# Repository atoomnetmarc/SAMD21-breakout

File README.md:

ATSAMD21G18A-AU breakout board with the physical layout inspired by the `Arduino MKR Zero`.

# Power supply

Supply power to 3V3 pin. Or supply power to 5V pin (or USB) and get free 3V3.

# Platformio

`platformio.ini`:
```ini
[env:mzeroUSB]
platform = atmelsam
board = mzeroUSB
```

# Pinout

| Arduino   | SAMD21    | Alternate |
| --:       | --:       | --:       |
| AREF      | PA03      |
| A0        | PA01      | DAC
| A1        | PB08      |
| A2        | PB09      |
| A3        | PA04      |
| A4        | PA05      |
| A5        | PB02      |
| RX        | PA11      | D0
| TX        | PA10      | D1
| ~D2       | PA08      | SDA2
| ~D3       | PA09      | SCL2
| ~D4       | PA14      |
| ~D5       | PA15      |
| D6        | PA20      |
| D7        | PA21      |
| ~D8       | PA06      |
| ~D9       | PA07      |
| ~D10      | PA18      |
| ~D11      | PA16      | SDA3
| ~D12      | PA19      |
| ~D13      | PA17      | SCL3
| SDA       | PA22      |
| SCL       | PA23      |
| MISO      | PA12      |
| MOSI      | PB10      |
| SCK       | PB11      |

# Soldering

Solder every component except U1, J2, J4 and J5. Begin with all the components on the bottom.

Clean board.

Apply current limited (50mA) 5V to GND and 5V pin. Current should be about 6mA. Measure voltage on 3V3 pin, it should be 3.3V. Disconnect. Connect USB, both LEDs should light up again.

Solder U1 carefully. Inspect U1 pins with microscope for shorts or missing soldered pins. Correct when found.

Clean again. Inspect again.

Measure all adjacent signal pins (on headers J4 and J5) for shorts: XIN21, XOUT32, A0, AREF, GND, 3V3, A1, A2, A3, A4, ~D8, ~D9, ~D2, ~D3, TX, RX, 3V3, GND, MOSI, SCK, MISO, PA13 (U1 pin 22), ~D4, ~D5, ~D11, ~D13, ~D10, ~D12, D6, D7, SDA, SCL, USB- (on D1), USB+ (on D2), GND, 3V3, PB22 (U1 pin 37), PB23 (U1 pin 38), PA27 (U1 pin 39), RST, PA28 (U1 pin 41), GND, VDDCORE (on C21), 3V3, CLK (on J2), DIO (on J2), A5 and PB03 (U1 pin 48). Correct shorts when found.

Apply current limited (50mA) to GND and 5V pin. Current should still be about 6mA.

# Bootloader

Before this board behaves like an `Arduino M0` (that you can program with the USB-port) you must first use the `Burn Bootloader`-function from the Arduino IDE. Choose the board `Arduino M0`, then choose your desired `Programmer` then choose `Burn Bootloader`.

# Invisible Blink

Connect USB. A new serial port should appear in the device manager.

Open the example Blink sketch and flash it to the MCU. Measure voltage on GND and ~D13, it should alternate between 0V and 3.3V.

# Done

Done!

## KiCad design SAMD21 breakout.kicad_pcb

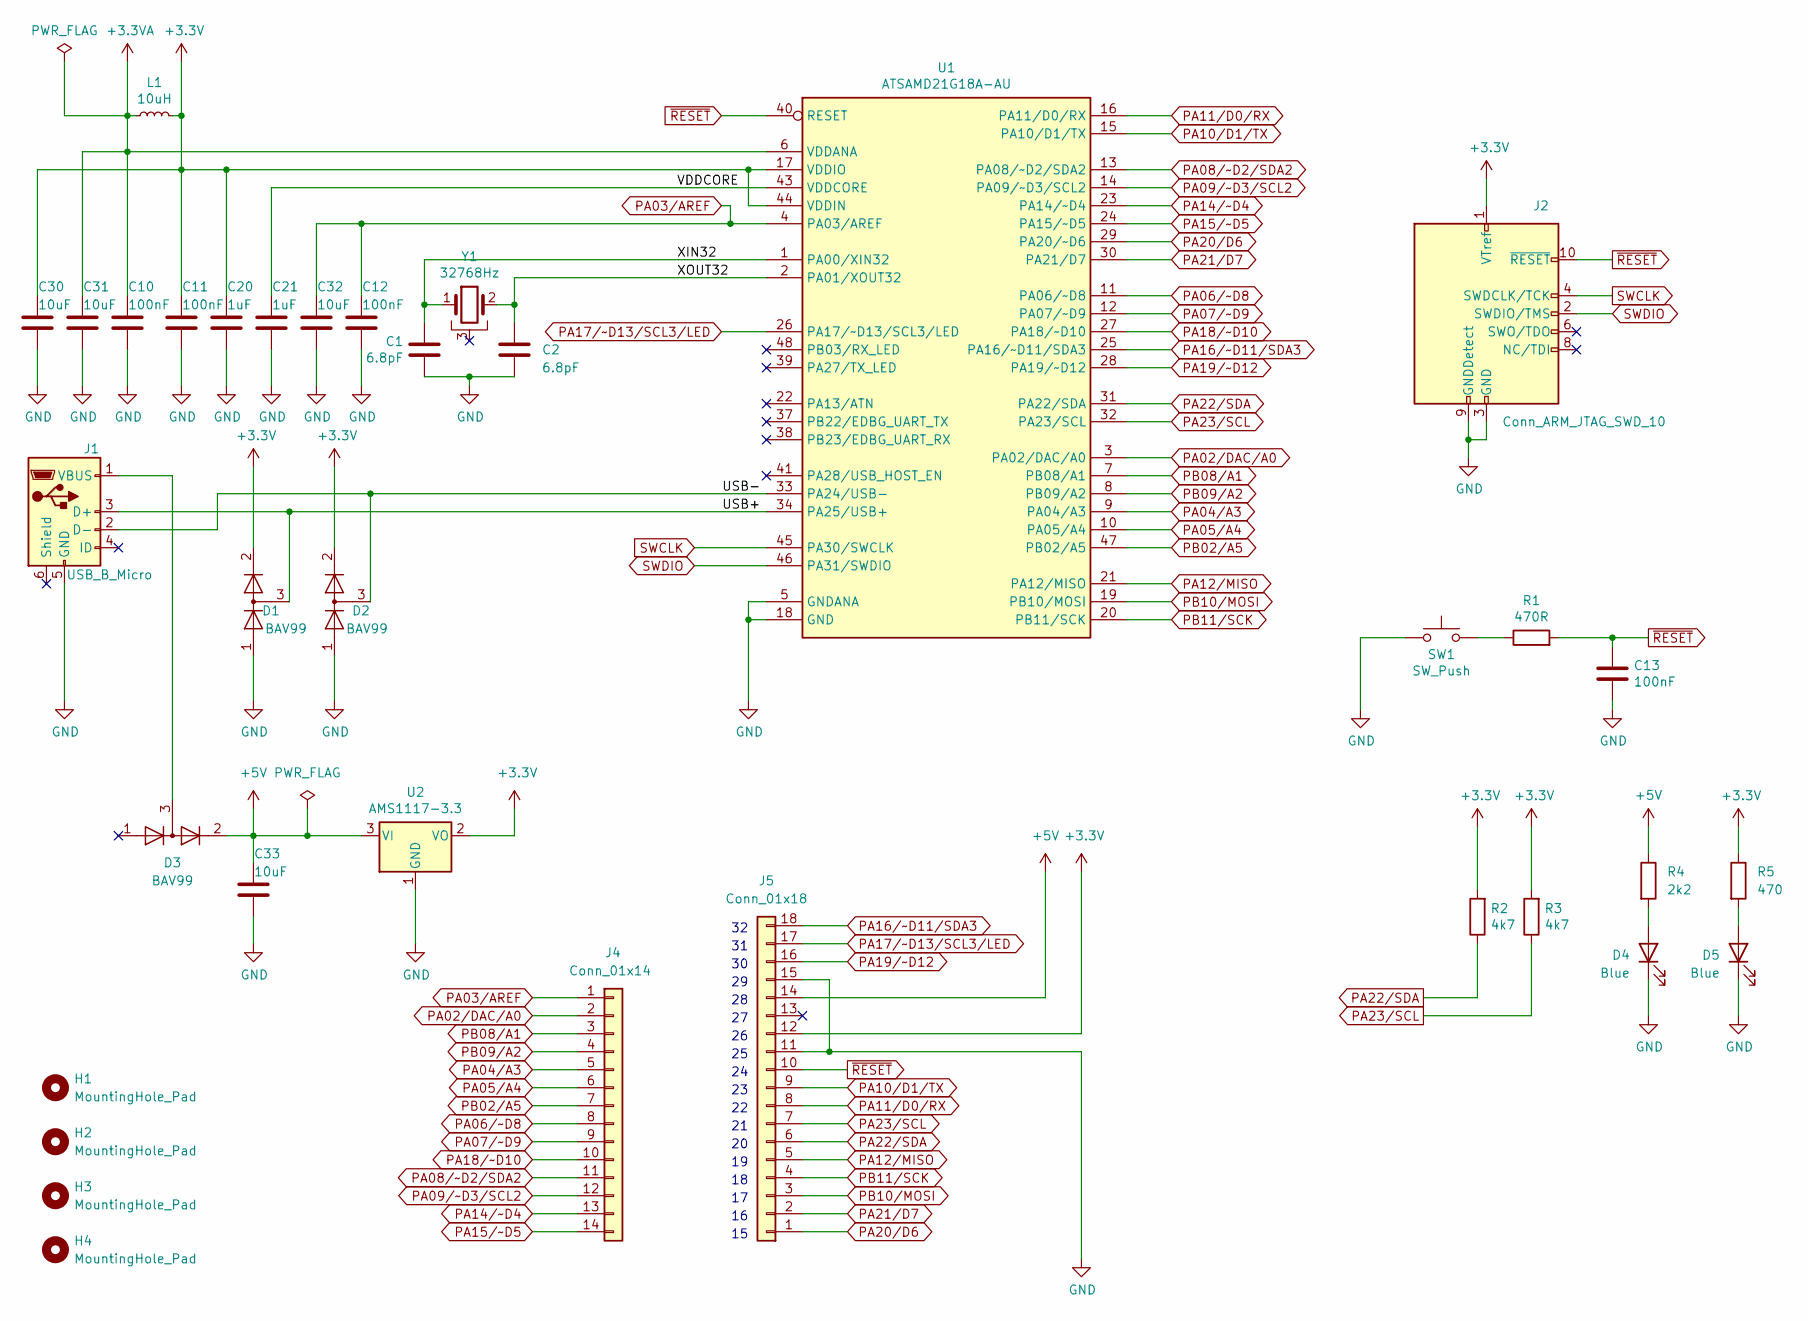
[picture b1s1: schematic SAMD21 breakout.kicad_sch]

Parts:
C1, C2: 6.8pF; C_0805_2012Metric_Pad1.18x1.45mm_HandSolder
C10, C11, C12, C13: 100nF; C_0805_2012Metric_Pad1.18x1.45mm_HandSolder
C20, C21: 1uF; C_0805_2012Metric_Pad1.18x1.45mm_HandSolder
C30, C31, C32, C33: 10uF; C_0805_2012Metric_Pad1.18x1.45mm_HandSolder
D1, D2, D3: BAV99; SOT-23
D4, D5: Blue; LED_0805_2012Metric_Pad1.15x1.40mm_HandSolder
H1, H2, H3, H4: MountingHole_Pad; MountingHole_2.2mm_M2_DIN965
J1: USB_B_Micro; USB_Micro-B_Amphenol_10118194_Horizontal
J2: Conn_ARM_JTAG_SWD_10; PinHeader_2x05_P2.54mm_Vertical
J4: Conn_01x14; PinHeader_1x14_P2.54mm_Vertical
J5: Conn_01x18; PinHeader_1x18_P2.54mm_Vertical
L1: 10uH; L_0805_2012Metric_Pad1.15x1.40mm_HandSolder
R1: 470R; R_0805_2012Metric_Pad1.20x1.40mm_HandSolder
R2, R3: 4k7; R_0805_2012Metric_Pad1.20x1.40mm_HandSolder
R4: 2k2; R_0805_2012Metric_Pad1.20x1.40mm_HandSolder
R5: 470; R_0805_2012Metric_Pad1.20x1.40mm_HandSolder
SW1: SW_Push; SW_SPST_CK_RS282G05A3
U1: ATSAMD21G18A-AU; TQFP-48_7x7mm_P0.5mm
U2: AMS1117-3.3; SOT-223-3_TabPinNC
Y1: 32768Hz; Crystal_C26-LF_D2.1mm_L6.5mm_Horizontal_1EP_style1

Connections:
+3.3V: C11.1, C20.1, C30.1, D1.2 (A), D2.2 (A), J2.1 (VTref), J5.12, L1.2, R2.2, R3.2, R5.1, U1.17 (VDDIO), U1.36 (VDDIO), U1.44 (VDDIN), U2.2 (VO)
+3.3VA: C10.1, C31.1, L1.1, U1.6 (VDDANA)
+5V: C33.1, D3.2 (A), J5.14, R4.1, U2.3 (VI)
/USB+: D1.3 (K), J1.3 (D+), U1.34 (PA25/USB+)
/USB-: D2.3 (K), J1.2 (D-), U1.33 (PA24/USB-)
/VDDCORE: C21.1, U1.43 (VDDCORE)
/XIN32: C1.1, U1.1 (PA00/XIN32), Y1.1
/XOUT32: C2.1, U1.2 (PA01/XOUT32), Y1.2
GND: C1.2, C2.2, C10.2, C11.2, C12.2, C13.2, C20.2, C21.2, C30.2, C31.2, C32.2, C33.2, D1.1 (K), D2.1 (K), D4.1 (K), D5.1 (K), J1.5 (GND), J2.3 (GND), J2.5 (GND), J2.9 (GNDDetect), J5.11, J5.15, SW1.1, U1.5 (GNDANA), U1.18 (GND), U1.35 (GND), U1.42 (GND), U2.1 (GND)
unnamed: D3.3 (K), J1.1 (VBUS)
unnamed: D4.2 (A), R4.2
unnamed: D5.2 (A), R5.2
unnamed: R1.1, SW1.2
PA02/DAC/A0: J4.2, U1.3 (PA02/DAC/A0)
PA03/AREF: C12.1, C32.1, J4.1, U1.4 (PA03/AREF)
PA04/A3: J4.5, U1.9 (PA04/A3)
PA05/A4: J4.6, U1.10 (PA05/A4)
PA06/~D8: J4.8, U1.11 (PA06/~D8)
PA07/~D9: J4.9, U1.12 (PA07/~D9)
PA08/~D2/SDA2: J4.11, U1.13 (PA08/~D2/SDA2)
PA09/~D3/SCL2: J4.12, U1.14 (PA09/~D3/SCL2)
PA10/D1/TX: J5.9, U1.15 (PA10/D1/TX)
PA11/D0/RX: J5.8, U1.16 (PA11/D0/RX)
PA12/MISO: J5.5, U1.21 (PA12/MISO)
PA14/~D4: J4.13, U1.23 (PA14/~D4)
PA15/~D5: J4.14, U1.24 (PA15/~D5)
PA16/~D11/SDA3: J5.18, U1.25 (PA16/~D11/SDA3)
PA17/~D13/SCL3/LED: J5.17, U1.26 (PA17/~D13/SCL3/LED)
PA18/~D10: J4.10, U1.27 (PA18/~D10)
PA19/~D12: J5.16, U1.28 (PA19/~D12)
PA20/D6: J5.1, U1.29 (PA20/~D6)
PA21/D7: J5.2, U1.30 (PA21/D7)
PA22/SDA: J5.6, R2.1, U1.31 (PA22/SDA)
PA23/SCL: J5.7, R3.1, U1.32 (PA23/SCL)
PB02/A5: J4.7, U1.47 (PB02/A5)
PB08/A1: J4.3, U1.7 (PB08/A1)
PB09/A2: J4.4, U1.8 (PB09/A2)
PB10/MOSI: J5.3, U1.19 (PB10/MOSI)
PB11/SCK: J5.4, U1.20 (PB11/SCK)
SWCLK: J2.4 (SWDCLK/TCK), U1.45 (PA30/SWCLK)
SWDIO: J2.2 (SWDIO/TMS), U1.46 (PA31/SWDIO)
~RESET: C13.1, J2.10 (~RESET), J5.10, R1.2, U1.40 (RESET)

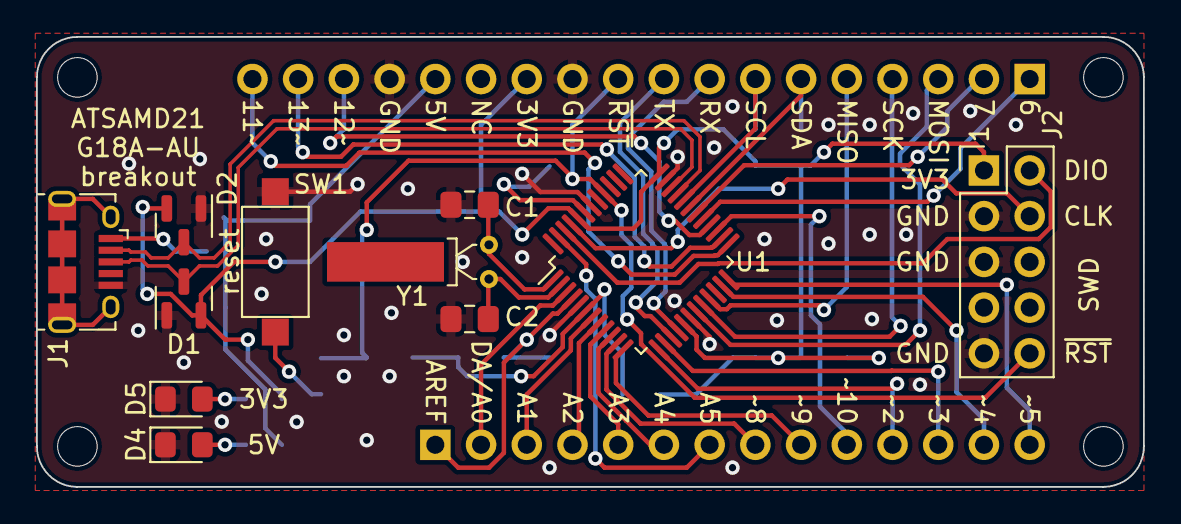
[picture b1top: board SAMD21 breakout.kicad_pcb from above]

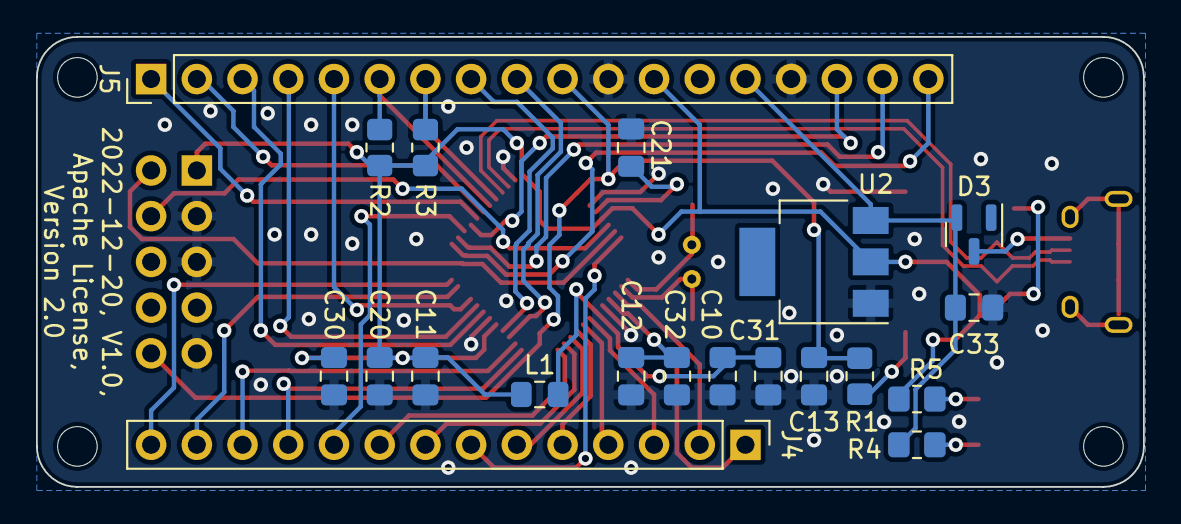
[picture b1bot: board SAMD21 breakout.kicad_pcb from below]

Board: 2 copper layers, 61.5 x 25.0 mm, 35 parts (20 on the bottom side), 42 nets.

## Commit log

2022-11-20 ignore zip
2022-12-09 Mounting holes do not need be on BOM.
2022-12-09 Add soldering, test and bootloader instructions.

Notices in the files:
README.md:
License: Apache 2.0
SAMD21 breakout.kicad_pcb:
2022-12-20, V1.0,
Apache License,
Version 2.0
